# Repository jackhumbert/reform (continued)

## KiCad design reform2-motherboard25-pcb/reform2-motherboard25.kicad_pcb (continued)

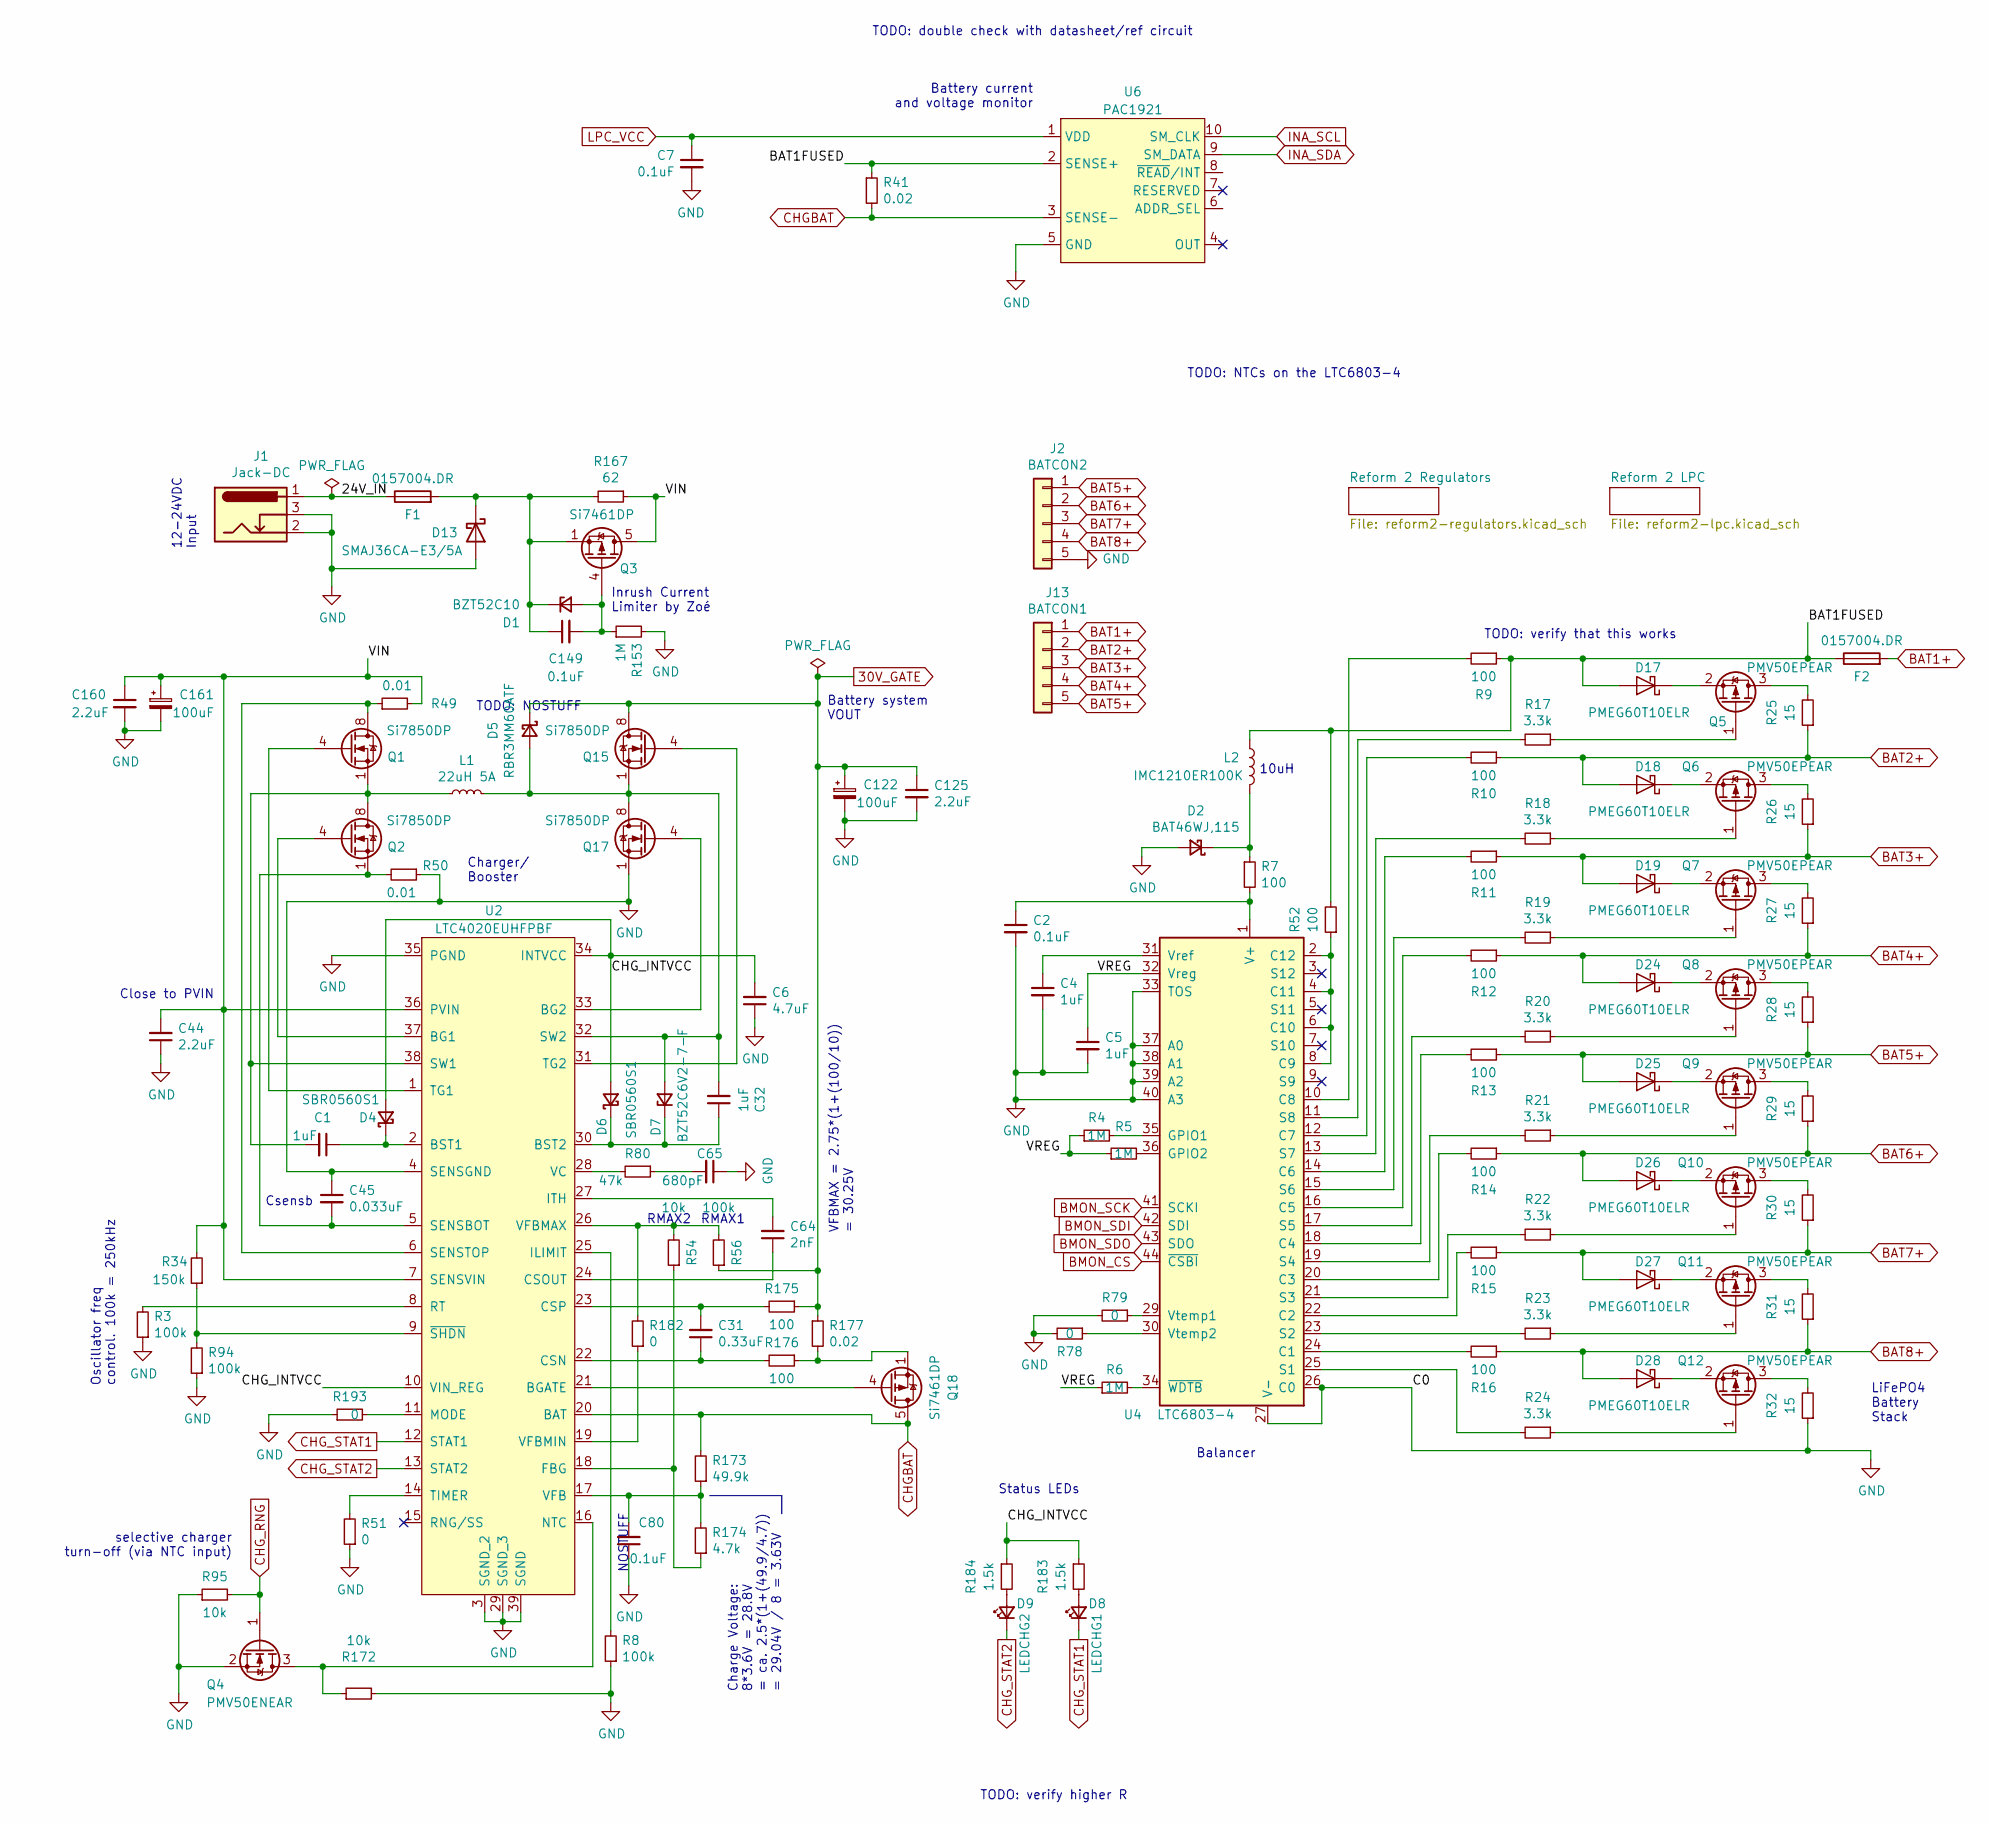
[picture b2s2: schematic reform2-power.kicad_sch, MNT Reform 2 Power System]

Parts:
C1, C4, C5, C32: 1uF; C_0603_1608Metric
C2, C7, C80, C149: 0.1uF; C_0603_1608Metric
C6: 4.7uF; C_0603_1608Metric
C31: 0.33uF; C_0603_1608Metric
C44, C125, C160: 2.2uF; C_0603_1608Metric
C45: 0.033uF; C_0603_1608Metric
C64: 2nF; C_0603_1608Metric
C65: 680pF; C_0603_1608Metric
C122, C161: 100uF; CP_Elec_6.3x7.7
D1: BZT52C10; D_SOD-123
D2: BAT46WJ,115; D_SOD-323
D4, D6: SBR0560S1; D_SOD-123
D5: RBR3MM60ATF; D_SOD-123
D7: BZT52C6V2-7-F; D_SOD-123
D8: LEDCHG1; LED_0603_1608Metric
D9: LEDCHG2; LED_0603_1608Metric
D13: SMAJ36CA-E3/5A; D_SMA
D17, D18, D19, D24, D25, D26, D27, D28: PMEG60T10ELR; Nexperia_CFP3_SOD-123W
F1, F2: 0157004.DR; fuse_smf
J1: Jack-DC; SWC_RAPC712X
J2: BATCON2; Molex_Pico-Lock_504050-0591_1x05-1MP_P1.50mm_Horizontal
J13: BATCON1; Molex_Pico-Lock_504050-0591_1x05-1MP_P1.50mm_Horizontal
L1: 22uH 5A; L_12x12mm_H6mm
L2: IMC1210ER100K; L_1210_3225Metric
Q1, Q2, Q15, Q17: Si7850DP; PowerPAK_SO-8_Single_8Pads
Q3, Q18: Si7461DP; PowerPAK_SO-8_Single_8Pads
Q4: PMV50ENEAR; SOT-23
Q5, Q6, Q7, Q8, Q9, Q10, Q11, Q12: PMV50EPEAR; SOT-23
R3, R8, R56, R94: 100k; R_0603_1608Metric
R4, R5, R6, R153: 1M; R_0603_1608Metric
R7, R9, R10, R11, R12, R13, R14, R15, R16, R52, R175, R176: 100; R_0603_1608Metric
R17, R18, R19, R20, R21, R22, R23, R24: 3.3k; R_0603_1608Metric
R25, R26, R27, R28, R29, R30, R31, R32: 15; R_2512_6332Metric
R34: 150k; R_0603_1608Metric
R41, R177: 0.02; R_0612_1632Metric
R49, R50: 0.01; R_0612_1632Metric
R51, R78, R79, R182, R193: 0; R_0603_1608Metric
R54, R95, R172: 10k; R_0603_1608Metric
R80: 47k; R_0603_1608Metric
R167: 62; R_0603_1608Metric
R173: 49.9k; R_0603_1608Metric
R174: 4.7k; R_0603_1608Metric
R183, R184: 1.5k; R_0603_1608Metric
U2: LTC4020EUHFPBF; QFN-38-1EP_5x7mm_P0.5mm_EP3.15x5.15mm
U4: LTC6803-4; SSOP-44_5.3x12.8mm_P0.5mm
U6: PAC1921

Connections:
30V_GATE: C122.1, C125.1, D5.1 (K), Q15.5 (D), Q15.6 (D), Q15.7 (D), Q15.8 (D), R56.1, R175.1, R177.1; also elsewhere on the board
/Reform 2 Power/24V_IN: F1.1, J1.1
/Reform 2 Power/BAT1FUSED: D17.2 (A), F2.1, L2.1, R9.1, R41.1, R52.2, U6.2 (SENSE+)
/Reform 2 Power/CHG_INTVCC: C6.2, D4.2 (A), D6.2 (A), R183.1, R184.1, U2.10 (VIN_REG), U2.34 (INTVCC)
/Reform 2 Power/VIN: C44.2, C160.1, C161.1, Q3.5 (D), Q3.6 (D), Q3.7 (D), Q3.8 (D), R34.2, R49.2, R167.1, U2.7 (SENSVIN), U2.36 (PVIN)
/Reform 2 Power/VREG: C5.1, R4.1, R5.1, R6.1, U4.32 (Vreg)
BAT1+: F2.2, J13.1
BAT2+: D18.2 (A), J13.2, R10.1, R25.1
BAT3+: D19.2 (A), J13.3, R11.1, R26.1
BAT4+: D24.2 (A), J13.4, R12.1, R27.1
BAT5+: D25.2 (A), J2.1, J13.5, R13.1, R28.1
BAT6+: D26.2 (A), J2.2, R14.1, R29.1
BAT7+: D27.2 (A), J2.3, R15.1, R30.1
BAT8+: D28.2 (A), J2.4, R16.1, R31.1
BMON_CS: U4.44 (~CSBI); also elsewhere on the board
BMON_SCK: U4.41 (SCKI); also elsewhere on the board
BMON_SDI: U4.42 (SDI); also elsewhere on the board
BMON_SDO: U4.43 (SDO); also elsewhere on the board
CHGBAT: Q18.5 (D), Q18.6 (D), Q18.7 (D), Q18.8 (D), R41.2, R173.2, U2.20 (BAT), U6.3 (SENSE-)
CHG_RNG: Q4.1 (G), R95.2; also elsewhere on the board
CHG_STAT1: D8.1 (K), U2.12 (STAT1)
CHG_STAT2: D9.1 (K), U2.13 (STAT2)
GND: C2.2, C4.2, C5.2, C6.1, C7.2, C44.1, C45.1, C65.1, C80.1, C122.2, C125.2, C160.2, C161.2, D2.2 (A), D13.2 (A), J1.2, J1.3, J2.5, Q4.2 (S), Q17.1 (S), Q17.2 (S), Q17.3 (S), R3.1, R8.1, R32.1, R50.1, R51.1, R78.2, R79.2, R94.1, R95.1, R153.2, R172.2, R193.1, U2.3 (SGND_2), U2.4 (SENSGND), U2.29 (SGND_3), U2.35 (PGND), U2.39 (SGND), U4.26 (C0), U4.27 (V-), U4.33 (TOS), U4.37 (A0), U4.38 (A1), U4.39 (A2), U4.40 (A3), U6.5 (GND); also elsewhere on the board
INA_SCL: U6.10 (SM_CLK); also elsewhere on the board
INA_SDA: U6.9 (SM_DATA); also elsewhere on the board
LPC_VCC: C7.1, U6.1 (VDD); also elsewhere on the board
unnamed: C1.1, D4.1 (K), U2.2 (BST1)
unnamed: C1.2, L1.1, Q1.1 (S), Q1.2 (S), Q1.3 (S), Q2.5 (D), Q2.6 (D), Q2.7 (D), Q2.8 (D), U2.38 (SW1)
unnamed: C2.1, R7.2, U4.1 (V+)
unnamed: C4.1, U4.31 (Vref)
unnamed: C31.1, R176.2, U2.22 (CSN)
unnamed: C31.2, R175.2, U2.23 (CSP)
unnamed: C32.1, D6.1 (K), D7.1 (K), U2.30 (BST2)
unnamed: C32.2, D5.2 (A), D7.2 (A), L1.2, Q15.1 (S), Q15.2 (S), Q15.3 (S), Q17.5 (D), Q17.6 (D), Q17.7 (D), Q17.8 (D), U2.32 (SW2)
unnamed: C45.2, Q2.1 (S), Q2.2 (S), Q2.3 (S), R50.2, U2.5 (SENSBOT)
unnamed: C64.1, U2.24 (CSOUT)
unnamed: C64.2, U2.27 (ITH)
unnamed: C65.2, R80.1
unnamed: C80.2, R173.1, R174.2, U2.17 (VFB)
unnamed: C149.1, D1.1 (K), D13.1 (K), F1.2, Q3.1 (S), Q3.2 (S), Q3.3 (S), R167.2
unnamed: C149.2, D1.2 (A), Q3.4 (G), R153.1
unnamed: D2.1 (K), L2.2, R7.1
unnamed: D8.2 (A), R183.2
unnamed: D9.2 (A), R184.2
unnamed: Q1.4 (G), U2.1 (TG1)
unnamed: Q1.5 (D), Q1.6 (D), Q1.7 (D), Q1.8 (D), R49.1, U2.6 (SENSTOP)
unnamed: Q2.4 (G), U2.37 (BG1)
unnamed: Q4.3 (D), R172.1, U2.16 (NTC)
unnamed: Q5.1 (G), R17.1
unnamed: D17.1 (K), Q5.2 (S)
unnamed: Q5.3 (D), R25.2
unnamed: Q6.1 (G), R18.1
unnamed: D18.1 (K), Q6.2 (S)
unnamed: Q6.3 (D), R26.2
unnamed: Q7.1 (G), R19.1
unnamed: D19.1 (K), Q7.2 (S)
unnamed: Q7.3 (D), R27.2
unnamed: Q8.1 (G), R20.1
unnamed: D24.1 (K), Q8.2 (S)
unnamed: Q8.3 (D), R28.2
unnamed: Q9.1 (G), R21.1
unnamed: D25.1 (K), Q9.2 (S)
unnamed: Q9.3 (D), R29.2
unnamed: Q10.1 (G), R22.1
unnamed: D26.1 (K), Q10.2 (S)
unnamed: Q10.3 (D), R30.2
unnamed: Q11.1 (G), R23.1
unnamed: D27.1 (K), Q11.2 (S)
unnamed: Q11.3 (D), R31.2
unnamed: Q12.1 (G), R24.1
unnamed: D28.1 (K), Q12.2 (S)
unnamed: Q12.3 (D), R32.2
unnamed: Q15.4 (G), U2.31 (TG2)
unnamed: Q17.4 (G), U2.33 (BG2)
unnamed: Q18.1 (S), Q18.2 (S), Q18.3 (S), R176.1, R177.2
unnamed: Q18.4 (G), U2.21 (BGATE)
unnamed: R3.2, U2.8 (RT)
unnamed: R4.2, U4.35 (GPIO1)
unnamed: R5.2, U4.36 (GPIO2)
unnamed: R6.2, U4.34 (~WDTB)
unnamed: R8.2, U2.25 (ILIMIT)
unnamed: R9.2, U4.10 (C8)
unnamed: R10.2, U4.12 (C7)
unnamed: R11.2, U4.14 (C6)
unnamed: R12.2, U4.16 (C5)
unnamed: R13.2, U4.18 (C4)
unnamed: R14.2, U4.20 (C3)
unnamed: R15.2, U4.22 (C2)
unnamed: R16.2, U4.24 (C1)
unnamed: R17.2, U4.11 (S8)
unnamed: R18.2, U4.13 (S7)
unnamed: R19.2, U4.15 (S6)
unnamed: R20.2, U4.17 (S5)
unnamed: R21.2, U4.19 (S4)
unnamed: R22.2, U4.21 (S3)
unnamed: R23.2, U4.23 (S2)
unnamed: R24.2, U4.25 (S1)
unnamed: R34.1, R94.2, U2.9 (~SHDN)
unnamed: R51.2, U2.14 (TIMER)
unnamed: R52.1, U4.2 (C12), U4.4 (C11), U4.6 (C10), U4.8 (C9)
unnamed: R78.1, U4.30 (Vtemp2)
unnamed: R79.1, U4.29 (Vtemp1)
unnamed: R80.2, U2.28 (VC)
unnamed: R54.1, R174.1, U2.18 (FBG)
unnamed: R182.1, U2.19 (VFBMIN)
unnamed: R54.2, R56.2, R182.2, U2.26 (VFBMAX)
unnamed: R193.2, U2.11 (MODE)

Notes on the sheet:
Oscillator freq control. 100k = 250kHz
TODO: double check with datasheet/ref circuit
Csensb
Charge Voltage: 8*3.6V = 28.8V = ca. 2.5*(1+(49.9/4.7)) = 29.04V / 8 = 3.63V
Close to PVIN
Battery current and voltage monitor
10uH
TODO: verify higher R
12-24VDC Input
Inrush Current Limiter by Zoé
LiFePO4 Battery Stack
Battery system VOUT
selective charger turn-off (via NTC input)
TODO: NTCs on the LTC6803-4
Status LEDs
VFBMAX = 2.75*(1+(100/10)) = 30.25V
RMAX2
RMAX1
Balancer
TODO: verify that this works
Charger/ Booster
TODO: NOSTUFF
NOSTUFF

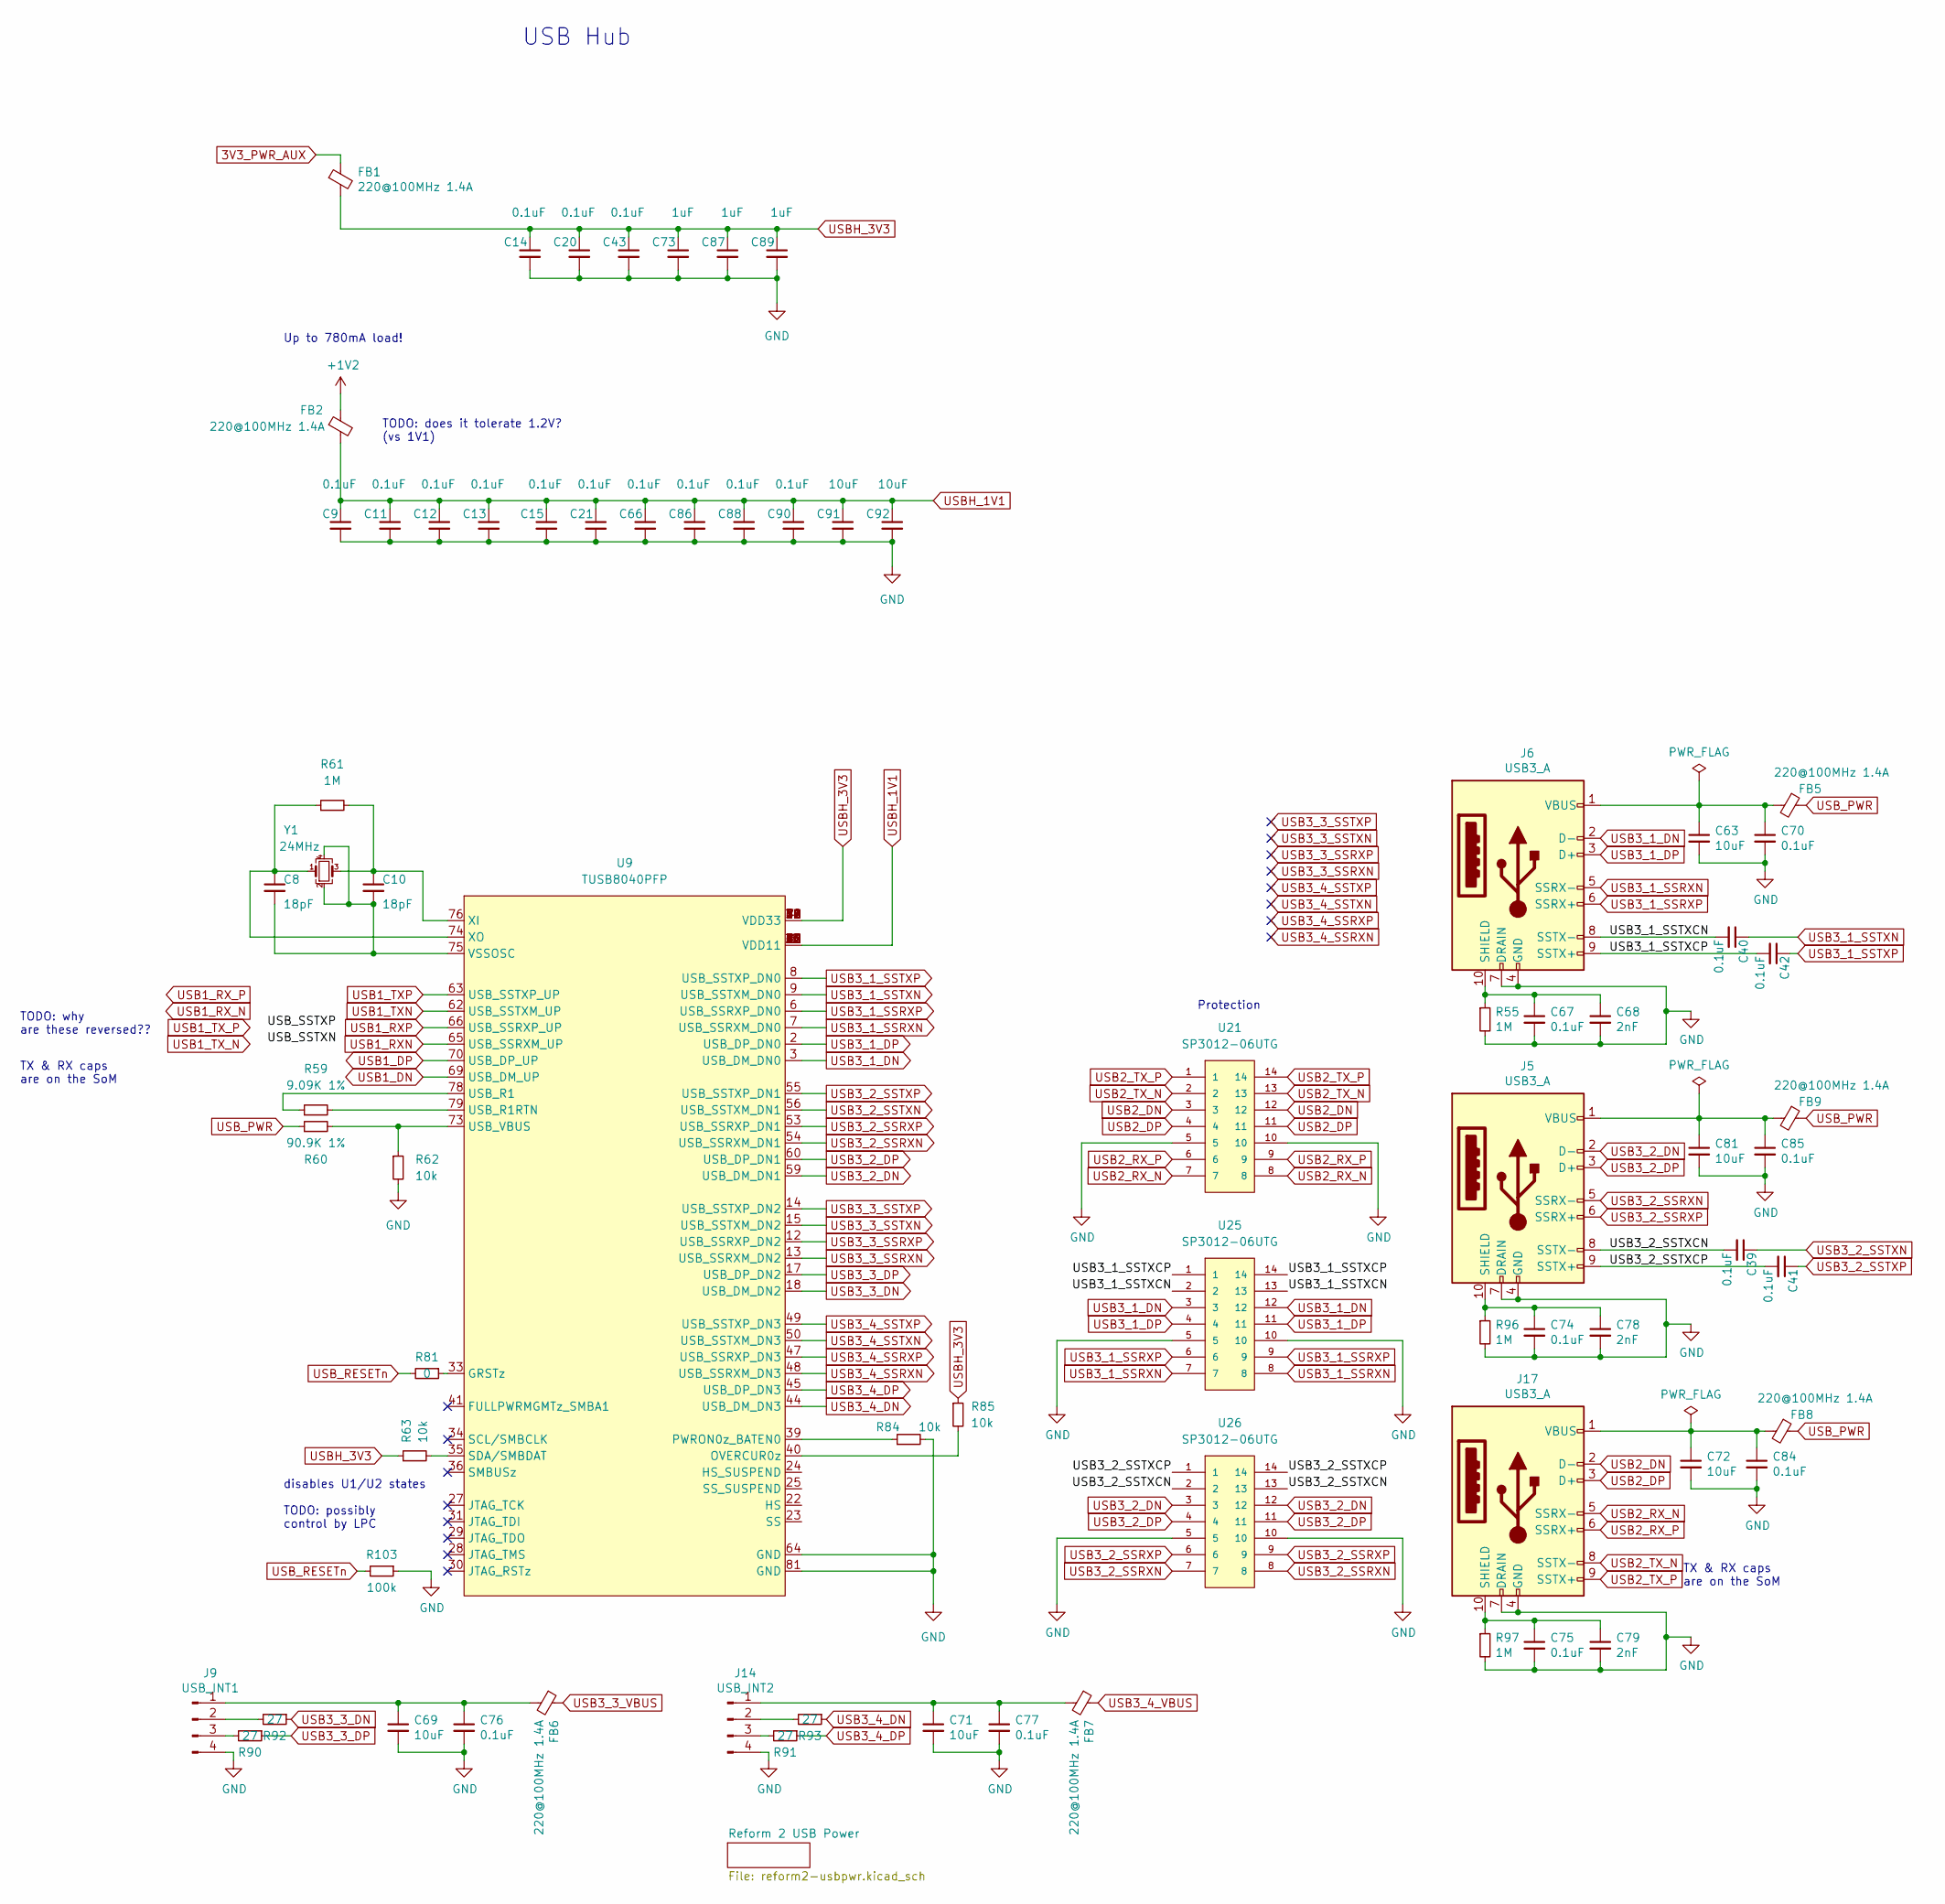
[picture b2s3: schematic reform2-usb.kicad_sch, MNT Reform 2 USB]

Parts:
C8, C10: 18pF; C_0603_1608Metric; LCSC C107040
C9, C11, C12, C13, C14, C15, C20, C21, C43, C66, C86, C88, C90: 0.1uF; C_0402_1005Metric; LCSC C1525
C39, C40, C41, C42, C67, C70, C74, C75, C76, C77, C84, C85: 0.1uF; C_0603_1608Metric
C63, C69, C71, C72, C81: 10uF; C_0603_1608Metric
C68, C78, C79: 2nF; C_0603_1608Metric
C73, C87, C89: 1uF; C_0402_1005Metric; LCSC C14445
C91, C92: 10uF; C_0402_1005Metric; LCSC C315248
FB1, FB2, FB5, FB6, FB7, FB8, FB9: 220@100MHz 1.4A; L_0603_1608Metric
J5, J6, J17: USB3_A; 692121030100
J9: USB_INT1; JST_PH_B4B-PH-K_1x04_P2.00mm_Vertical
J14: USB_INT2; JST_PH_B4B-PH-K_1x04_P2.00mm_Vertical
R55, R96, R97: 1M; R_0603_1608Metric
R59: 9.09K 1%; R_0402_1005Metric; LCSC C400642
R60: 90.9K 1%; R_0402_1005Metric; LCSC C26989
R61: 1M; R_0402_1005Metric; LCSC C144787
R62, R63, R84, R85: 10k; R_0402_1005Metric; LCSC C60490
R81: 0; R_0402_1005Metric; LCSC C242160
R90, R91, R92, R93: 27; R_0603_1608Metric
R103: 100k; R_0603_1608Metric
U9: TUSB8040PFP; QFP50P1400X1400X120-81N; LCSC C2872001
U21, U25, U26: SP3012-06UTG; SON50P350X135X55-14N
Y1: 24MHz; Crystal_SMD_Abracon_ABM8G-4Pin_3.2x2.5mm; LCSC C91744

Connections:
3V3_PWR_AUX: FB1.1; also elsewhere on the board
+1V2: FB2.1; also elsewhere on the board
/Reform 2 USB/USB3_1_SSTXCN: C40.2, J6.8 (SSTX-), U25.2, U25.13
/Reform 2 USB/USB3_1_SSTXCP: C42.2, J6.9 (SSTX+), U25.1, U25.14
/Reform 2 USB/USB3_2_SSTXCN: C39.2, J5.8 (SSTX-), U26.2, U26.13
/Reform 2 USB/USB3_2_SSTXCP: C41.2, J5.9 (SSTX+), U26.1, U26.14
GND: C9.2, C11.2, C12.2, C13.2, C14.2, C15.2, C20.2, C21.2, C43.2, C63.2, C66.2, C67.2, C68.2, C69.2, C70.2, C71.2, C72.2, C73.2, C74.2, C75.2, C76.2, C77.2, C78.2, C79.2, C81.2, C84.2, C85.2, C86.2, C87.2, C88.2, C89.2, C90.2, C91.2, C92.2, J5.4 (GND), J5.7 (DRAIN), J6.4 (GND), J6.7 (DRAIN), J9.4, J14.4, J17.4 (GND), J17.7 (DRAIN), R55.2, R62.2, R84.2, R96.2, R97.2, R103.1, U9.64 (GND), U9.81 (GND), U21.5, U21.10, U25.5, U25.10, U26.5, U26.10; also elsewhere on the board
unnamed: C8.1, R61.1, U9.74 (XO), Y1.1
unnamed: C10.1, R61.2, U9.76 (XI), Y1.3
unnamed: C8.2, C10.2, U9.75 (VSSOSC), Y1.2, Y1.4
unnamed: C63.1, C70.1, FB5.2, J6.1 (VBUS)
unnamed: C67.1, C68.1, J6.10 (SHIELD), R55.1
unnamed: C69.1, C76.1, FB6.2, J9.1
unnamed: C71.1, C77.1, FB7.2, J14.1
unnamed: C72.1, C84.1, FB8.2, J17.1 (VBUS)
unnamed: C74.1, C78.1, J5.10 (SHIELD), R96.1
unnamed: C75.1, C79.1, J17.10 (SHIELD), R97.1
unnamed: C81.1, C85.1, FB9.2, J5.1 (VBUS)
unnamed: J9.2, R92.2
unnamed: J9.3, R90.2
unnamed: J14.2, R93.2
unnamed: J14.3, R91.2
unnamed: R59.1, U9.78 (USB_R1)
unnamed: R59.2, U9.79 (USB_R1RTN)
unnamed: R60.2, R62.1, U9.73 (USB_VBUS)
unnamed: R63.2, U9.35 (SDA/SMBDAT)
unnamed: R81.1, U9.33 (GRSTz)
unnamed: R84.1, U9.39 (PWRON0z_BATEN0)
unnamed: R85.2, U9.40 (OVERCUR0z)
USB1_DN: U9.69 (USB_DM_UP); also elsewhere on the board
USB1_DP: U9.70 (USB_DP_UP); also elsewhere on the board
USB1_RXN: U9.65 (USB_SSRXM_UP)
USB1_RXP: U9.66 (USB_SSRXP_UP)
USB1_TXN: U9.62 (USB_SSTXM_UP)
USB1_TXP: U9.63 (USB_SSTXP_UP)
USB2_DN: J17.2 (D-), U21.3, U21.12; also elsewhere on the board
USB2_DP: J17.3 (D+), U21.4, U21.11; also elsewhere on the board
USB2_RX_N: J17.5 (SSRX-), U21.7, U21.8; also elsewhere on the board
USB2_RX_P: J17.6 (SSRX+), U21.6, U21.9; also elsewhere on the board
USB2_TX_N: J17.8 (SSTX-), U21.2, U21.13; also elsewhere on the board
USB2_TX_P: J17.9 (SSTX+), U21.1, U21.14; also elsewhere on the board
USB3_1_DN: J6.2 (D-), U9.3 (USB_DM_DN0), U25.3, U25.12
USB3_1_DP: J6.3 (D+), U9.2 (USB_DP_DN0), U25.4, U25.11
USB3_1_SSRXN: J6.5 (SSRX-), U9.7 (USB_SSRXM_DN0), U25.7, U25.8
USB3_1_SSRXP: J6.6 (SSRX+), U9.6 (USB_SSRXP_DN0), U25.6, U25.9
USB3_1_SSTXN: C40.1, U9.9 (USB_SSTXM_DN0)
USB3_1_SSTXP: C42.1, U9.8 (USB_SSTXP_DN0)
USB3_2_DN: J5.2 (D-), U9.59 (USB_DM_DN1), U26.3, U26.12
USB3_2_DP: J5.3 (D+), U9.60 (USB_DP_DN1), U26.4, U26.11
USB3_2_SSRXN: J5.5 (SSRX-), U9.54 (USB_SSRXM_DN1), U26.7, U26.8
USB3_2_SSRXP: J5.6 (SSRX+), U9.53 (USB_SSRXP_DN1), U26.6, U26.9
USB3_2_SSTXN: C39.1, U9.56 (USB_SSTXM_DN1)
USB3_2_SSTXP: C41.1, U9.55 (USB_SSTXP_DN1)
USB3_3_DN: R92.1, U9.18 (USB_DM_DN2)
USB3_3_DP: R90.1, U9.17 (USB_DP_DN2)
USB3_3_SSRXN: U9.13 (USB_SSRXM_DN2)
USB3_3_SSRXP: U9.12 (USB_SSRXP_DN2)
USB3_3_SSTXN: U9.15 (USB_SSTXM_DN2)
USB3_3_SSTXP: U9.14 (USB_SSTXP_DN2)
USB3_3_VBUS: FB6.1
USB3_4_DN: R93.1, U9.44 (USB_DM_DN3)
USB3_4_DP: R91.1, U9.45 (USB_DP_DN3)
USB3_4_SSRXN: U9.48 (USB_SSRXM_DN3)
USB3_4_SSRXP: U9.47 (USB_SSRXP_DN3)
USB3_4_SSTXN: U9.50 (USB_SSTXM_DN3)
USB3_4_SSTXP: U9.49 (USB_SSTXP_DN3)
USB3_4_VBUS: FB7.1
USBH_1V1: C9.1, C11.1, C12.1, C13.1, C15.1, C21.1, C66.1, C86.1, C88.1, C90.1, C91.1, C92.1, FB2.2, U9.1 (VDD11), U9.5 (VDD11), U9.10 (VDD11), U9.11 (VDD11), U9.16 (VDD11), U9.20 (VDD11), U9.26 (VDD11), U9.32 (VDD11), U9.37 (VDD11), U9.42 (VDD11), U9.46 (VDD11), U9.51 (VDD11), U9.52 (VDD11), U9.57 (VDD11), U9.61 (VDD11), U9.67 (VDD11), U9.71 (VDD11)
USBH_3V3: C14.1, C20.1, C43.1, C73.1, C87.1, C89.1, FB1.2, R63.1, R85.1, U9.4 (VDD33), U9.19 (VDD33), U9.21 (VDD33), U9.38 (VDD33), U9.43 (VDD33), U9.58 (VDD33), U9.68 (VDD33), U9.72 (VDD33), U9.77 (VDD33), U9.80 (VDD33)
USB_PWR: FB5.1, FB8.1, FB9.1, R60.1; also elsewhere on the board
USB_RESETn: R81.2, R103.2; also elsewhere on the board

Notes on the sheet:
USB Hub
Up to 780mA load!
TODO: does it tolerate 1.2V? (vs 1V1)
TX & RX caps are on the SoM
disables U1/U2 states TODO: possibly control by LPC
TODO: why are these reversed??
Protection

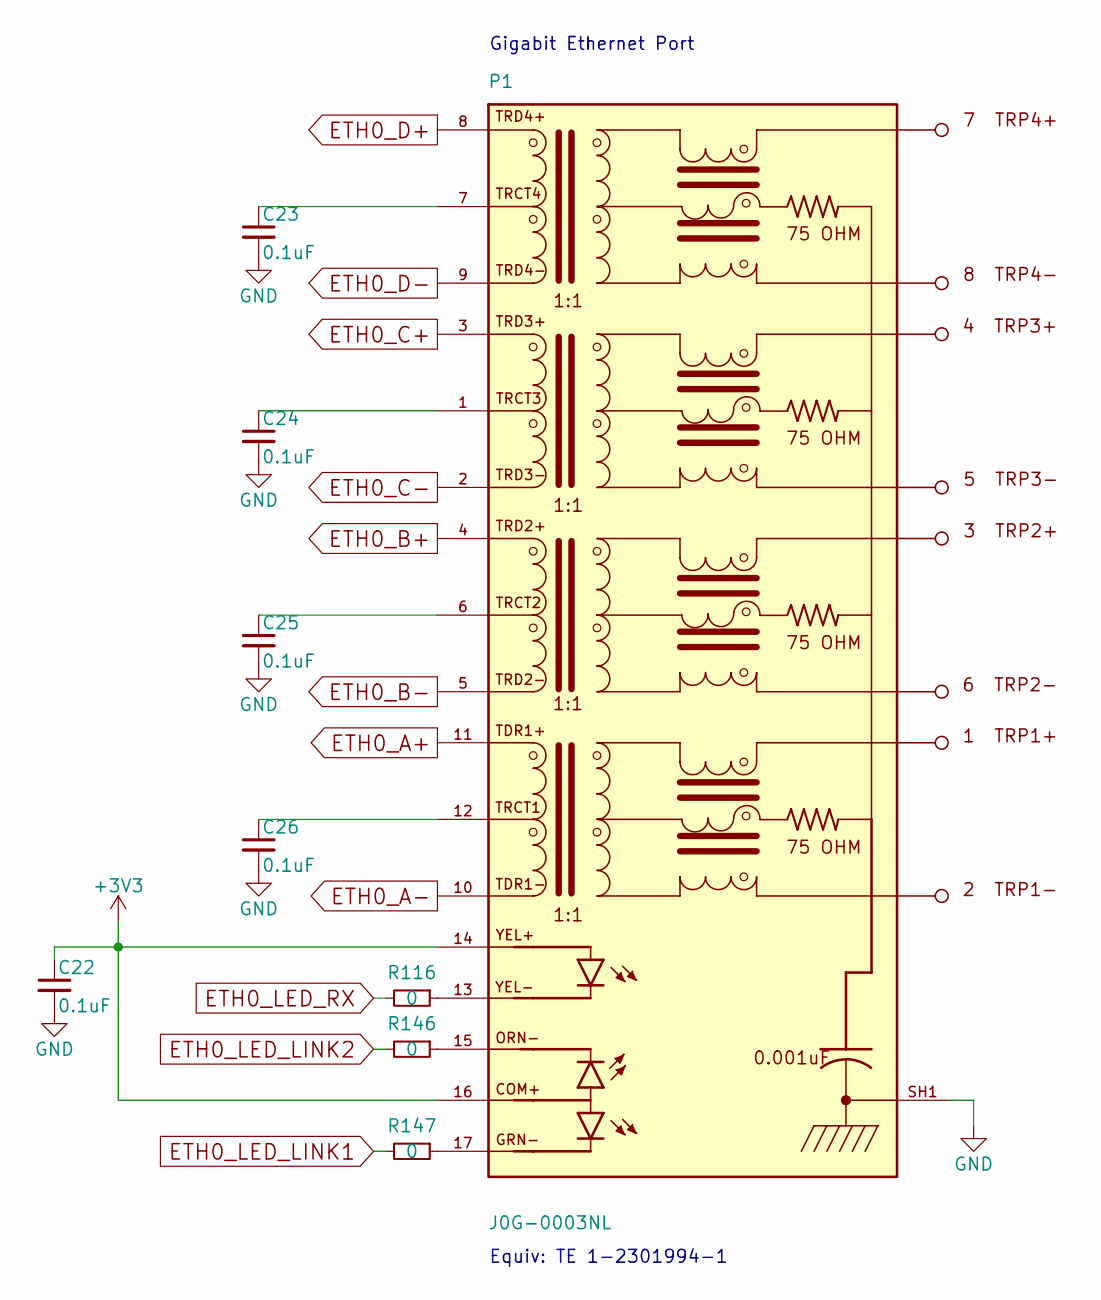
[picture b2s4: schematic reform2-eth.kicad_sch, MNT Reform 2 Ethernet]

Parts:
C22, C23, C24, C25, C26: 0.1uF; C_0603_1608Metric
P1: J0G-0003NL; PULSE_J0G-0003NL
R116, R146, R147: 0; R_0603_1608Metric

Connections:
+3V3: C22.1, P1.14 (YEL+), P1.16 (COM+); also elsewhere on the board
ETH0_A+: P1.11 (TDR1+); also elsewhere on the board
ETH0_A-: P1.10 (TDR1-); also elsewhere on the board
ETH0_B+: P1.4 (TRD2+); also elsewhere on the board
ETH0_B-: P1.5 (TRD2-); also elsewhere on the board
ETH0_C+: P1.3 (TRD3+); also elsewhere on the board
ETH0_C-: P1.2 (TRD3-); also elsewhere on the board
ETH0_D+: P1.8 (TRD4+); also elsewhere on the board
ETH0_D-: P1.9 (TRD4-); also elsewhere on the board
ETH0_LED_LINK1: R147.2; also elsewhere on the board
ETH0_LED_LINK2: R146.2; also elsewhere on the board
ETH0_LED_RX: R116.2; also elsewhere on the board
GND: C22.2, C23.2, C24.2, C25.2, C26.2, P1.SH1 (SHIELD), P1.SH2 (SHIELD); also elsewhere on the board
unnamed: C23.1, P1.7 (TRCT4)
unnamed: C24.1, P1.1 (TRCT3)
unnamed: C25.1, P1.6 (TRCT2)
unnamed: C26.1, P1.12 (TRCT1)
unnamed: P1.13 (YEL-), R116.1
unnamed: P1.15 (ORN-), R146.1
unnamed: P1.17 (GRN-), R147.1

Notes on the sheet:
Equiv: TE 1-2301994-1
Gigabit Ethernet Port

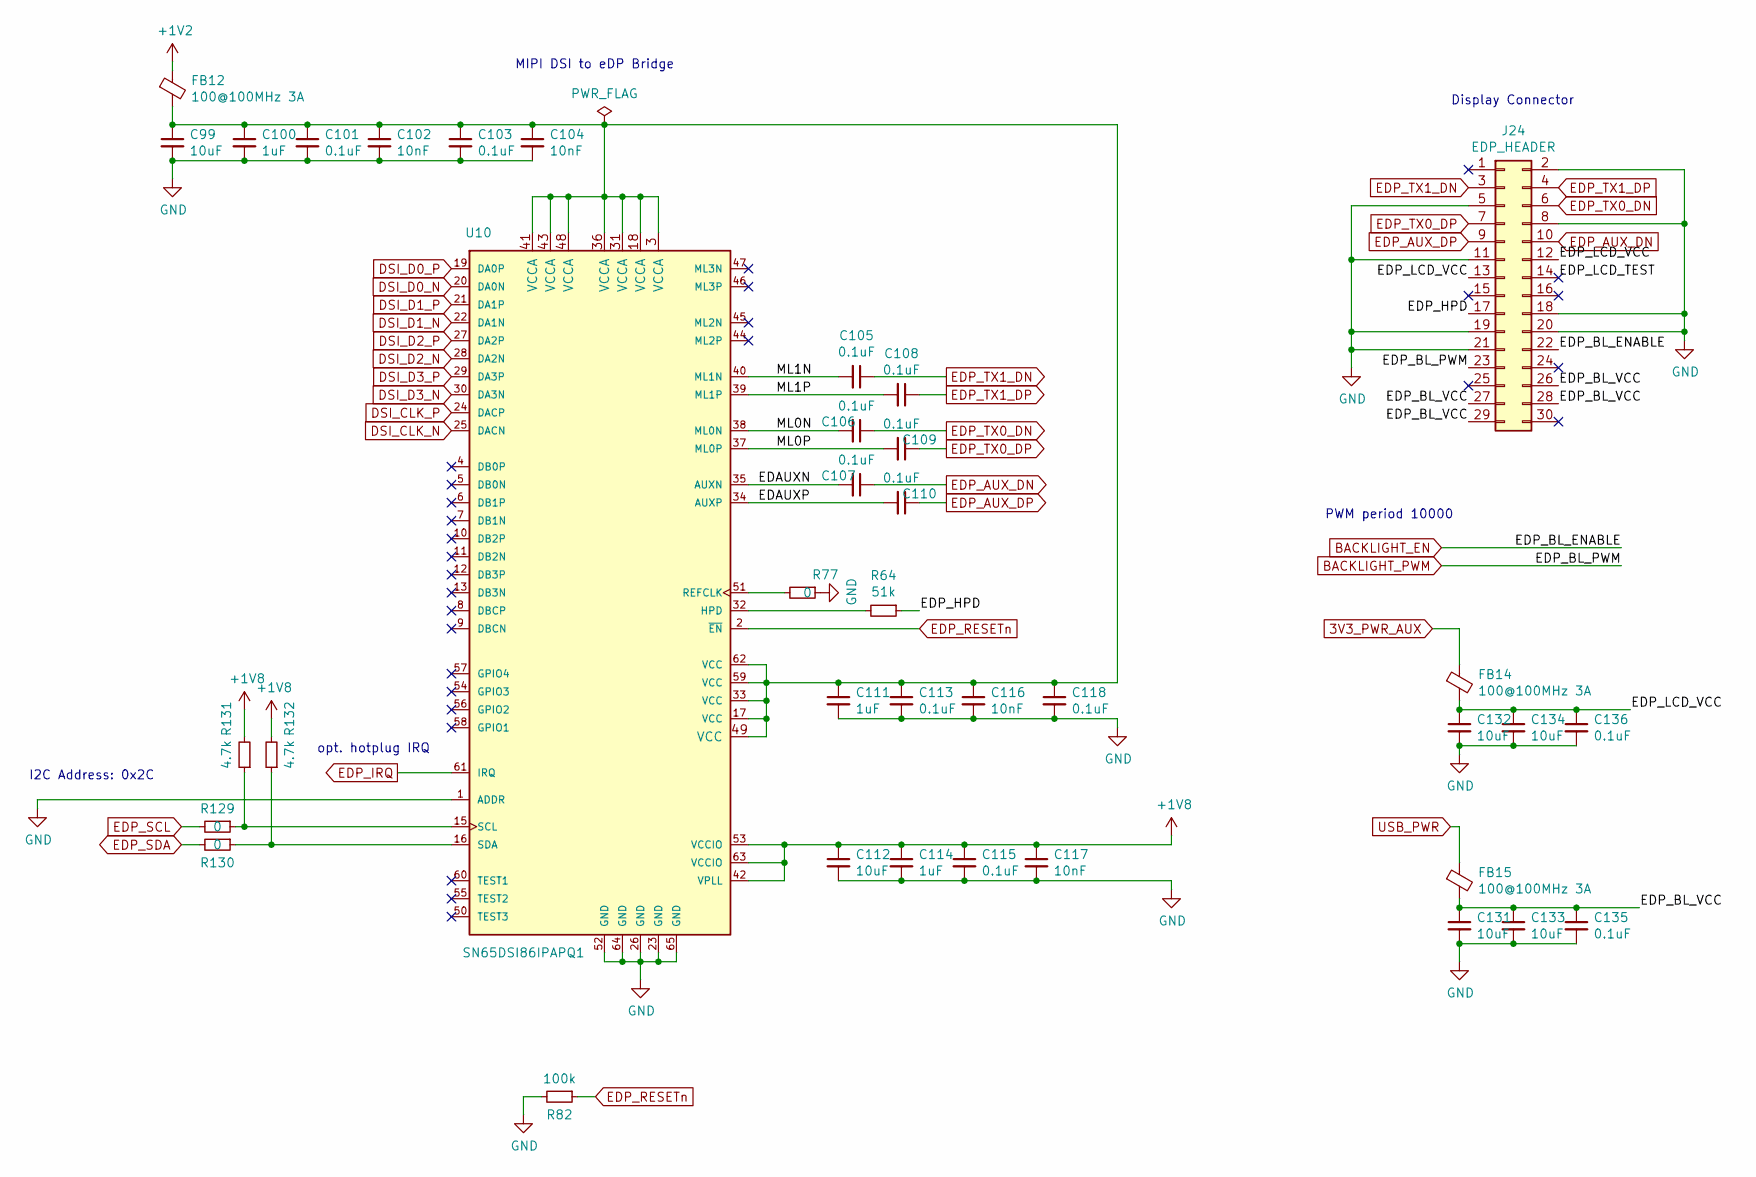
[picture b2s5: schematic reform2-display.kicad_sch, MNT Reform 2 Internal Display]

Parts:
C99, C112, C131, C132, C133, C134: 10uF; C_0603_1608Metric
C100, C111, C114: 1uF; C_0603_1608Metric
C101, C103, C105, C106, C107, C108, C109, C110, C113, C115, C118, C135, C136: 0.1uF; C_0603_1608Metric
C102, C104, C116, C117: 10nF; C_0603_1608Metric
FB12, FB14, FB15: 100@100MHz 3A; L_0603_1608Metric
J24: EDP_HEADER; PinHeader_2x15_P2.00mm_Vertical
R64: 51k; R_0603_1608Metric
R77, R129, R130: 0; R_0603_1608Metric
R82: 100k; R_0603_1608Metric
R131, R132: 4.7k; R_0603_1608Metric
U10: SN65DSI86IPAPQ1; HTQFP-64-1EP_10x10mm_P0.5mm_EP8x8mm

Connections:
3V3_PWR_AUX: FB14.1; also elsewhere on the board
+1V2: FB12.1; also elsewhere on the board
+1V8: C112.1, C114.1, C115.1, C117.1, R131.2, R132.2, U10.42 (VPLL), U10.53 (VCCIO), U10.63 (VCCIO); also elsewhere on the board
/Reform 2 Display/EDAUXN: C107.2, U10.35 (AUXN)
/Reform 2 Display/EDAUXP: C110.2, U10.34 (AUXP)
/Reform 2 Display/EDP_BL_VCC: C131.1, C133.1, C135.1, FB15.2, J24.26, J24.27, J24.28, J24.29
/Reform 2 Display/EDP_HPD: J24.17, R64.1
/Reform 2 Display/EDP_LCD_TEST: J24.14
/Reform 2 Display/EDP_LCD_VCC: C132.1, C134.1, C136.1, FB14.2, J24.12, J24.13
/Reform 2 Display/ML0N: C106.2, U10.38 (ML0N)
/Reform 2 Display/ML0P: C109.2, U10.37 (ML0P)
/Reform 2 Display/ML1N: C105.2, U10.40 (ML1N)
/Reform 2 Display/ML1P: C108.2, U10.39 (ML1P)
BACKLIGHT_EN: J24.22; also elsewhere on the board
BACKLIGHT_PWM: J24.23; also elsewhere on the board
DSI_CLK_N: U10.25 (DACN); also elsewhere on the board
DSI_CLK_P: U10.24 (DACP); also elsewhere on the board
DSI_D0_N: U10.20 (DA0N); also elsewhere on the board
DSI_D0_P: U10.19 (DA0P); also elsewhere on the board
DSI_D1_N: U10.22 (DA1N); also elsewhere on the board
DSI_D1_P: U10.21 (DA1P); also elsewhere on the board
DSI_D2_N: U10.28 (DA2N); also elsewhere on the board
DSI_D2_P: U10.27 (DA2P); also elsewhere on the board
DSI_D3_N: U10.30 (DA3N); also elsewhere on the board
DSI_D3_P: U10.29 (DA3P); also elsewhere on the board
EDP_AUX_DN: C107.1, J24.10
EDP_AUX_DP: C110.1, J24.9
EDP_IRQ: U10.61 (IRQ); also elsewhere on the board
EDP_RESETn: R82.1, U10.2 (~EN); also elsewhere on the board
EDP_SCL: R129.2; also elsewhere on the board
EDP_SDA: R130.2; also elsewhere on the board
EDP_TX0_DN: C106.1, J24.6
EDP_TX0_DP: C109.1, J24.7
EDP_TX1_DN: C105.1, J24.3
EDP_TX1_DP: C108.1, J24.4
GND: C99.2, C100.2, C101.2, C102.2, C103.2, C104.2, C111.2, C112.2, C113.2, C114.2, C115.2, C116.2, C117.2, C118.2, C131.2, C132.2, C133.2, C134.2, C135.2, C136.2, J24.2, J24.5, J24.8, J24.11, J24.18, J24.19, J24.20, J24.21, R77.1, R82.2, U10.1 (ADDR), U10.23 (GND), U10.26 (GND), U10.52 (GND), U10.64 (GND), U10.65 (GND); also elsewhere on the board
unnamed: C99.1, C100.1, C101.1, C102.1, C103.1, C104.1, C111.1, C113.1, C116.1, C118.1, FB12.2, U10.3 (VCCA), U10.17 (VCC), U10.18 (VCCA), U10.31 (VCCA), U10.33 (VCC), U10.36 (VCCA), U10.41 (VCCA), U10.43 (VCCA), U10.48 (VCCA), U10.49 (VCC), U10.59 (VCC), U10.62 (VCC)
unnamed: R64.2, U10.32 (HPD)
unnamed: R77.2, U10.51 (REFCLK)
unnamed: R129.1, R131.1, U10.15 (SCL)
unnamed: R130.1, R132.1, U10.16 (SDA)
USB_PWR: FB15.1; also elsewhere on the board

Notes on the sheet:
PWM period 10000
MIPI DSI to eDP Bridge
opt. hotplug IRQ
Display Connector
I2C Address: 0x2C
